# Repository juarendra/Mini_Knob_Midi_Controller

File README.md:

# Mini_Knob_Midi_Controller

## Preview Design 
<p align="center">

</p>
## Preview Product 
<p align="center">

</p>

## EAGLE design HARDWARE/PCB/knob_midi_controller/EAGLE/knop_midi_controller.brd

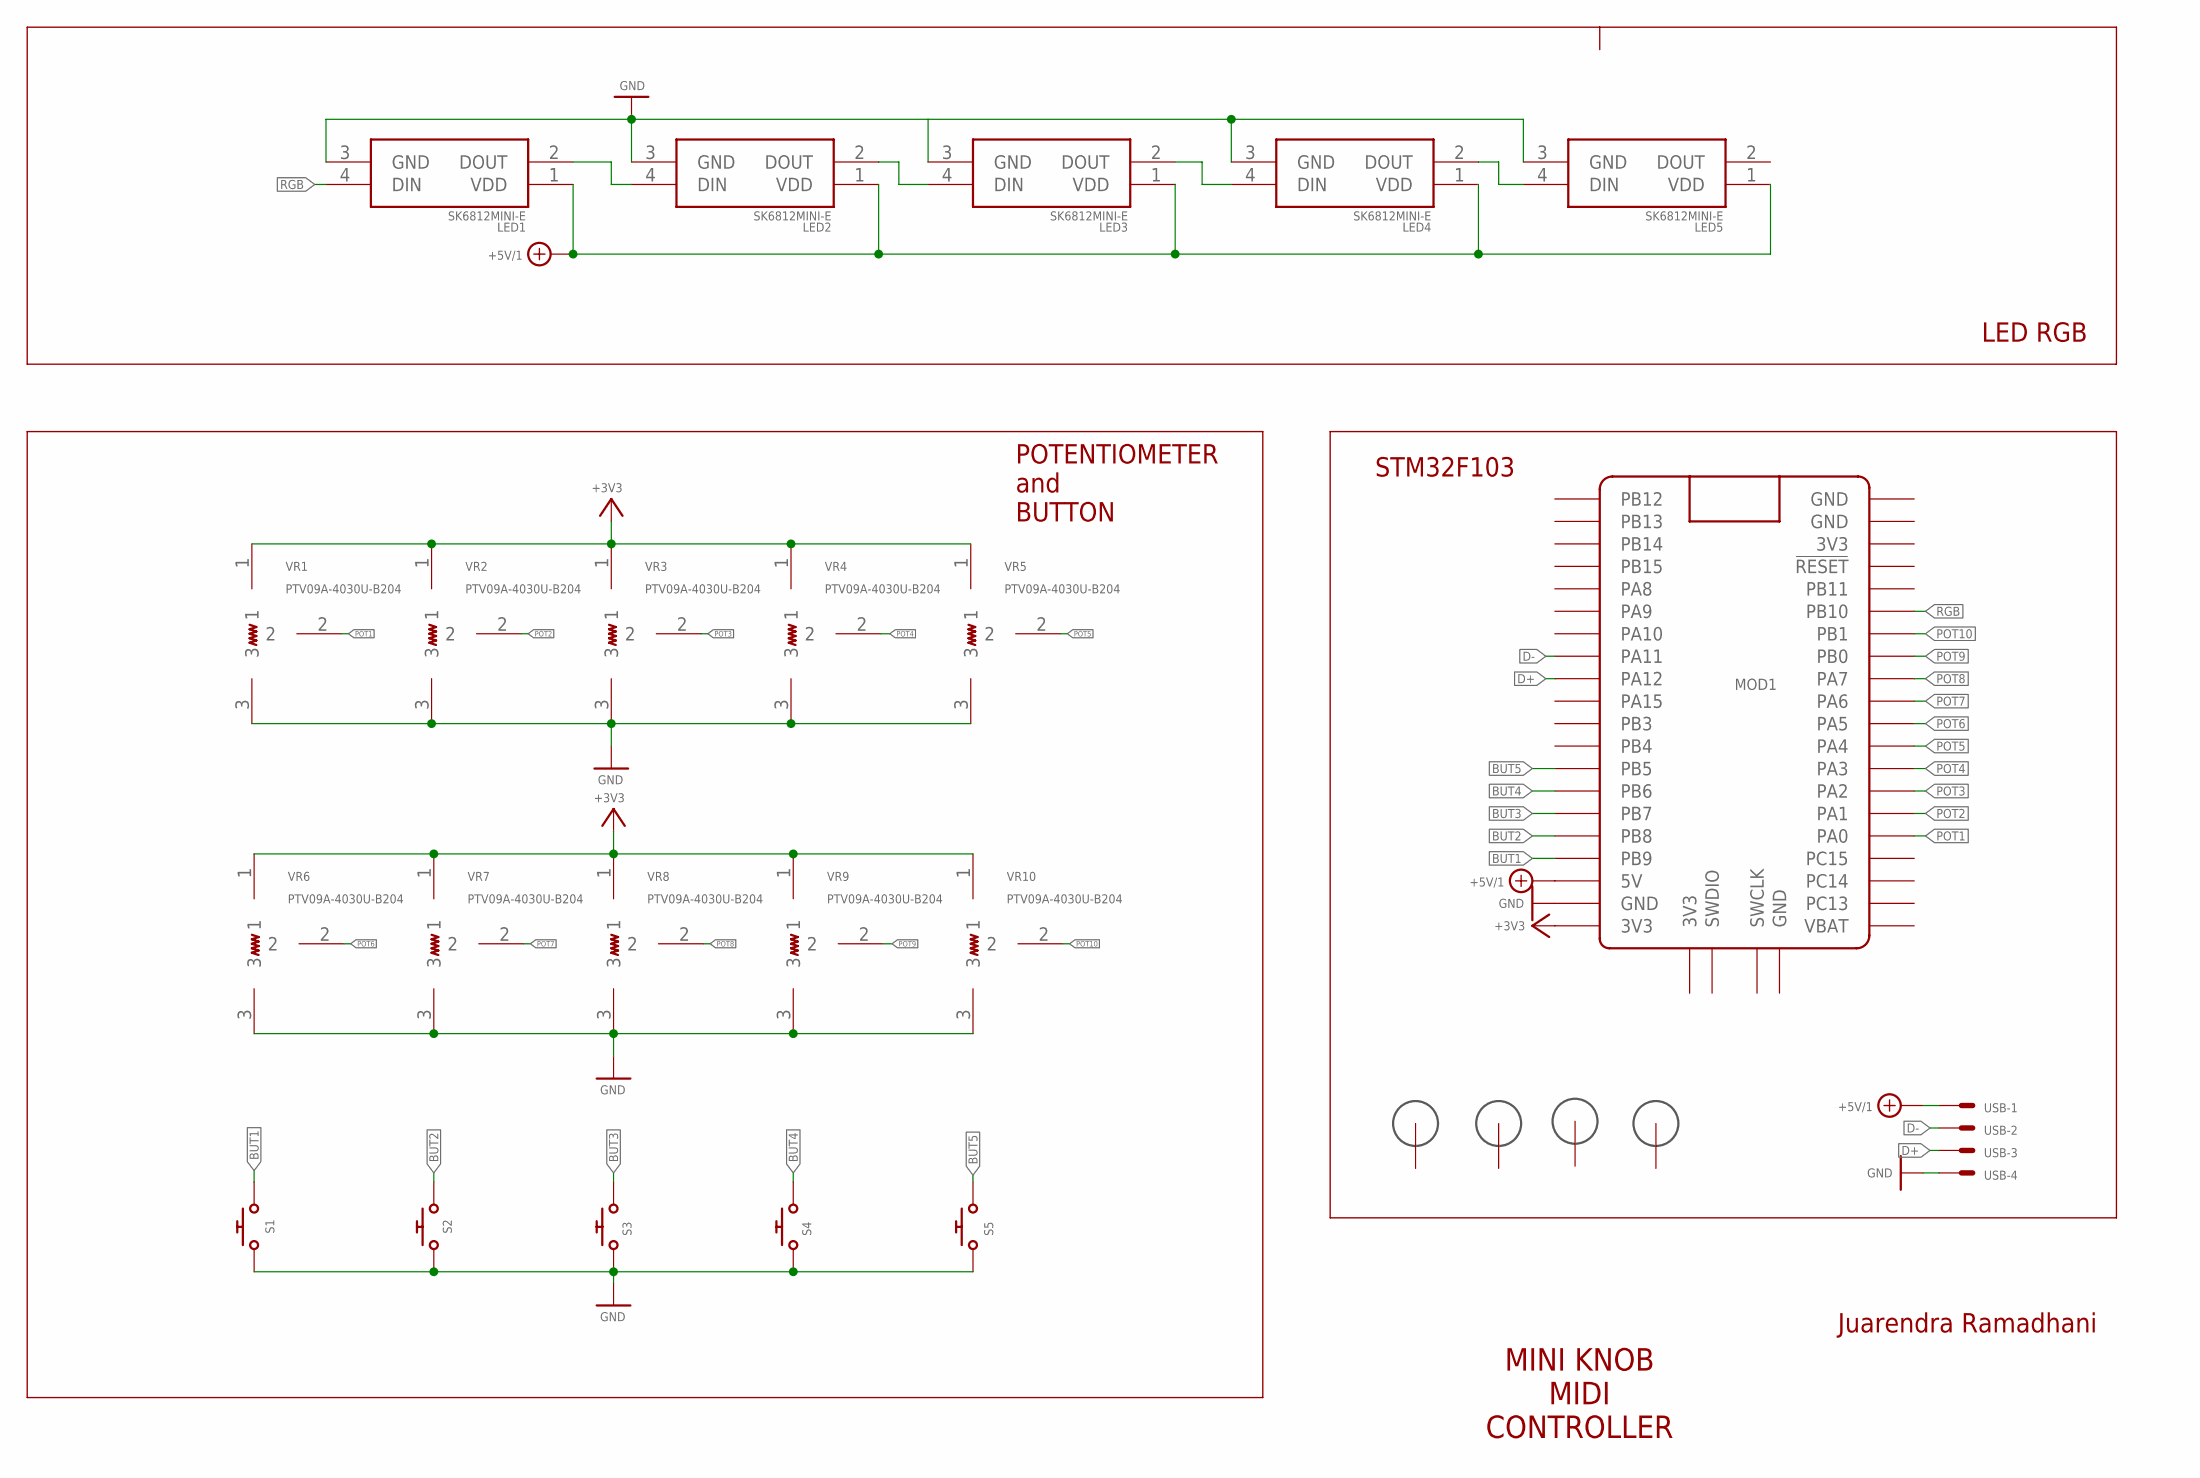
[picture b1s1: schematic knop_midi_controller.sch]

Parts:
H1, H2, H3, H4: 3MM_HOLE
LED1, LED2, LED3, LED4, LED5: SK6812MINI-E; SK6812MINIE
MOD1: BLUE_PILL
S1, S2, S3, S4, S5: CHERRY_MX_WITH_KEILWITH_KEIL; CHERRY_MX_WITH_KEIL
USB: 22-23-2041
VR1, VR2, VR3, VR4, VR5, VR6, VR7, VR8, VR9, VR10: PTV09A-4030U-B204; PTV09A4020FB103

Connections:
+3V3: MOD1.P$20 (3V3), VR1.1, VR2.1, VR3.1, VR4.1, VR5.1, VR6.1, VR7.1, VR8.1, VR9.1, VR10.1
+5V/1: LED1.1 (VDD), LED2.1 (VDD), LED3.1 (VDD), LED4.1 (VDD), LED5.1 (VDD), MOD1.P$18 (5V), USB.1
BUT1: MOD1.P$17 (PB9), S1.2
BUT2: MOD1.P$16 (PB8), S2.2
BUT3: MOD1.P$15 (PB7), S3.2
BUT4: MOD1.P$14 (PB6), S4.2
BUT5: MOD1.P$13 (PB5), S5.2
D+: MOD1.P$9 (PA12), USB.3
D-: MOD1.P$8 (PA11), USB.2
GND: LED1.3 (GND), LED2.3 (GND), LED3.3 (GND), LED4.3 (GND), LED5.3 (GND), MOD1.P$19 (GND), S1.1, S2.1, S3.1, S4.1, S5.1, USB.4, VR1.3, VR2.3, VR3.3, VR4.3, VR5.3, VR6.3, VR7.3, VR8.3, VR9.3, VR10.3
unnamed: LED1.2 (DOUT), LED2.4 (DIN)
unnamed: LED2.2 (DOUT), LED3.4 (DIN)
unnamed: LED3.2 (DOUT), LED4.4 (DIN)
unnamed: LED4.2 (DOUT), LED5.4 (DIN)
POT1: MOD1.P$36 (PA0), VR1.2
POT2: MOD1.P$35 (PA1), VR2.2
POT3: MOD1.P$34 (PA2), VR3.2
POT4: MOD1.P$33 (PA3), VR4.2
POT5: MOD1.P$32 (PA4), VR5.2
POT6: MOD1.P$31 (PA5), VR6.2
POT7: MOD1.P$30 (PA6), VR7.2
POT8: MOD1.P$29 (PA7), VR8.2
POT9: MOD1.P$28 (PB0), VR9.2
POT10: MOD1.P$27 (PB1), VR10.2
RGB: LED1.4 (DIN), MOD1.P$26 (PB10)

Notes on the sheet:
LED RGB
POTENTIOMETER and BUTTON
STM32F103
MINI KNOB MIDI CONTROLLER
Juarendra Ramadhani

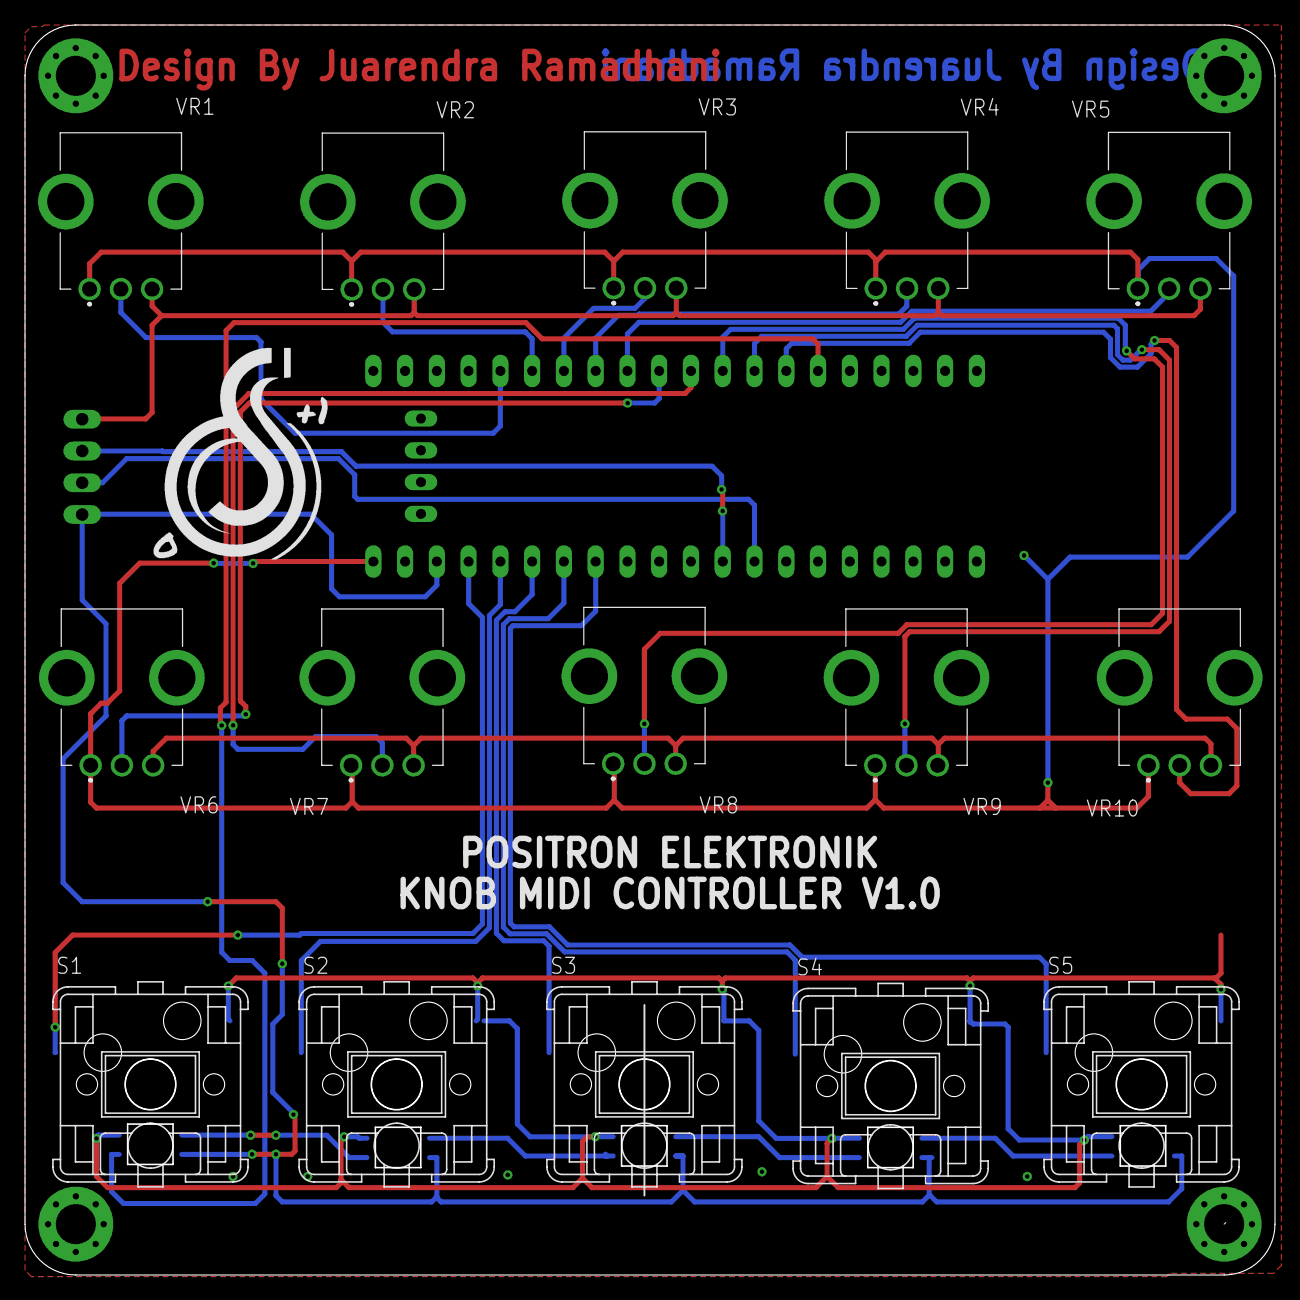
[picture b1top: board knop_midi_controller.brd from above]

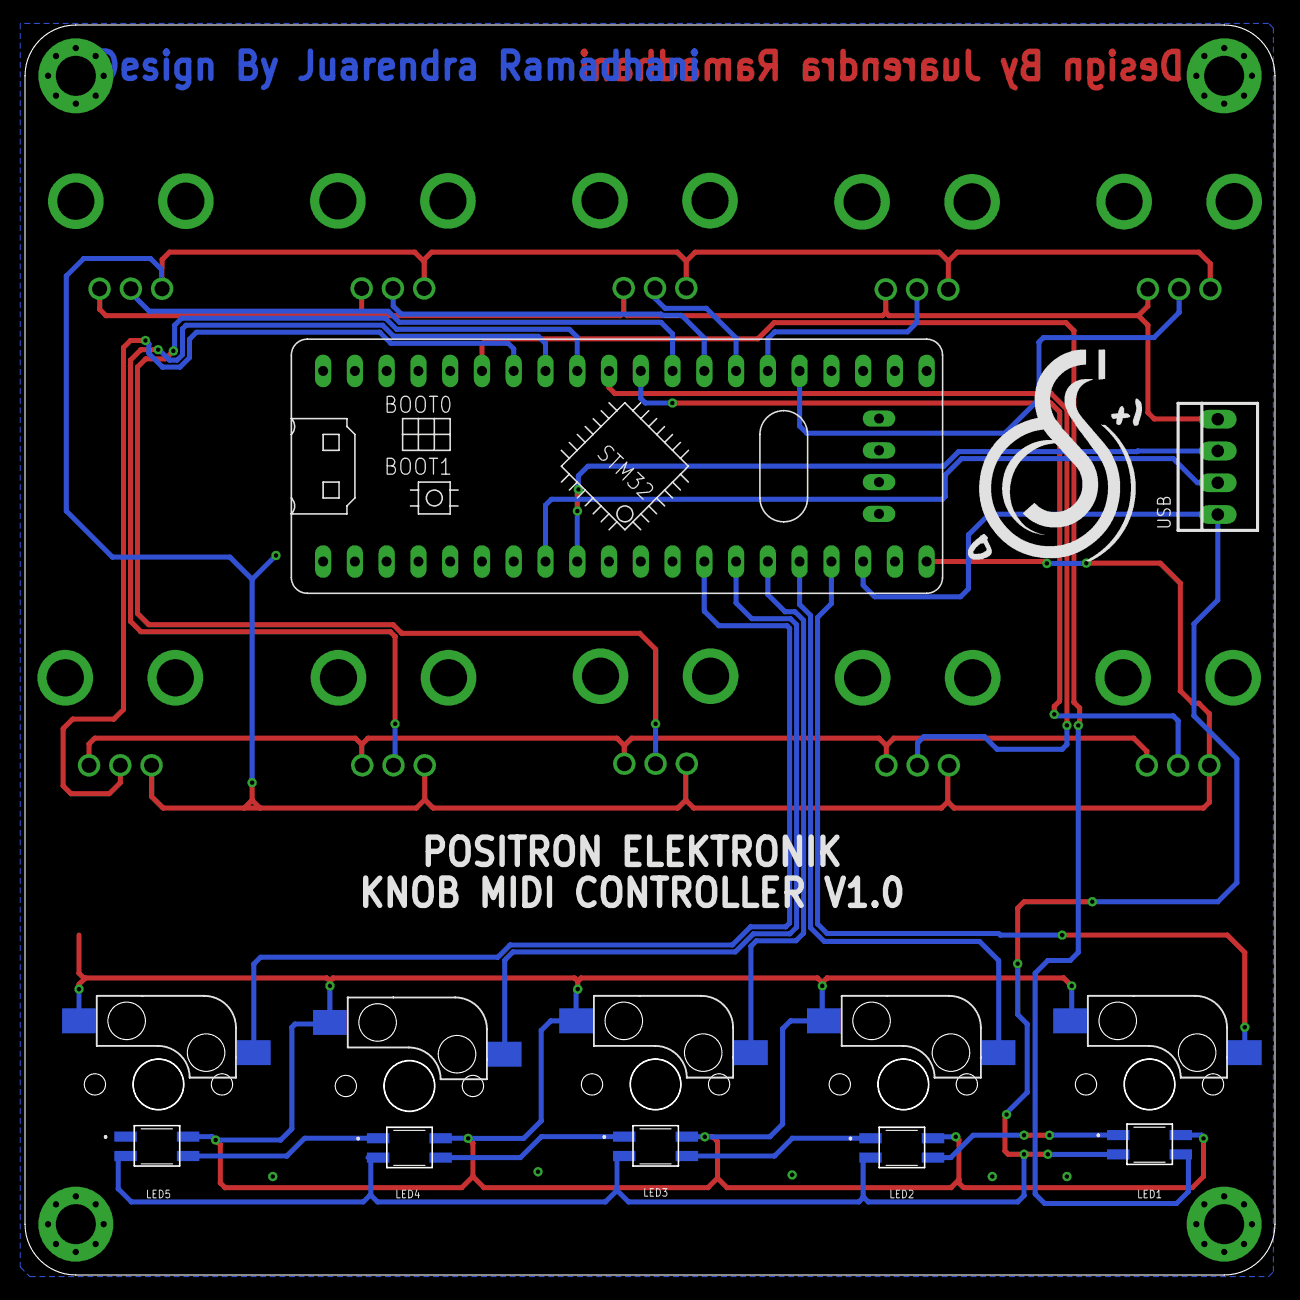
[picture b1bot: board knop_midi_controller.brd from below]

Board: 2 copper layers, 99.8 x 99.8 mm, 26 parts (8 on the bottom side), 25 nets.

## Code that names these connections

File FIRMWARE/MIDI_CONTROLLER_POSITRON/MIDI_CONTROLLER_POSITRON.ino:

#include <USBComposite.h>
USBMIDI midi;
//#include <ResponsiveAnalogRead.h> 
#include <FastLED.h>

#define LED_PIN     PB10        // Choose a tested pin
#define NUM_LEDS    5
#define BRIGHTNESS  100
#define LED_TYPE    WS2812B
#define COLOR_ORDER GRB

CRGB leds[NUM_LEDS];

const int NUM_POT = 10;
const int NUM_BUT = 5;
const int analogInputs[NUM_POT] = {PA0, PA1, PA2, PA3, PA4, PA5, PA6, PA7, PB0, PB1};
const int digitalInput[NUM_BUT] = {PB9, PB8, PB7, PB6, PB5};
int analogSliderValues[NUM_POT];
//ResponsiveAnalogRead responsivePot[NUM_POT] = {}; 
int potCState[NUM_POT] = { 0 };  // Current state of the pot
int potPState[NUM_POT] = { 0 };  // Previous state of the pot
int potVar = 0;                 // Difference between the current and previous state of the pot

int midiCState[NUM_POT] = { 0 };  // Current state of the midi value
int midiPState[NUM_POT] = { 0 };  // Previous state of the midi value
int reading_pot = 0;

const int TIMEOUT = 300;              // Amount of time the potentiometer will be read after it exceeds the varThreshold
const int varThreshold = 20;          // Threshold for the potentiometer signal variation
boolean potMoving = true;             // If the potentiometer is moving
unsigned long PTime[NUM_POT] = { 0 };  // Previously stored time
unsigned long timer[NUM_POT] = { 0 };  // Stores the time that has elapsed since the timer was reset

int potMin = 0;
int potMax = 3070;

bool debug_pot = false;
byte midiCh = 0;
byte cc = 1;   
byte NUM_BANK = 0;

const int NUM_SAMPLES = 10;

void setup() {
  FastLED.addLeds<LED_TYPE, LED_PIN, COLOR_ORDER>(leds, NUM_LEDS);
  FastLED.setBrightness(BRIGHTNESS);

  for (int i = 0; i < NUM_POT; i++) {
    pinMode(analogInputs[i], INPUT);
  }
  for (int i = 0; i < NUM_BUT; i++) {
    pinMode(digitalInput[i], INPUT_PULLUP);
  }
  if (debug_pot){
    Serial.begin(9600);
  }
  else{
    USBComposite.setProductId(0x0031);
    midi.begin();
    while (!USBComposite);
  }
}

void loop() {
  // Light up LEDs based on active bank
  for(int i = 0; i < NUM_LEDS; i++) {
    if (i == NUM_BANK) {
      leds[i] = CRGB::White;   // Active bank LED to white
    } else {
      leds[i] = CRGB::Black;   // Others off
    }
  }
  FastLED.show();

  for (int i = 0; i < NUM_BUT; i++){
    if (!digitalRead(digitalInput[i])){
      NUM_BANK = i;
    }

  }
  if(debug_pot){
    updateSliderValues();
    printSliderValues();
    delay(100);
  }
  else {
    sendMidiValue();
    delay(10);
  }
}

void sendMidiValue() {
  int potMin = 10;    
  int potMax = 3070;

  for (int i = 0; i < NUM_POT; i++) {
    int total = 0;

    // Take multiple samples to average
    for (int s = 0; s < NUM_SAMPLES; s++) {
      total += analogRead(analogInputs[i]);
      delayMicroseconds(100); // Small delay between reads
    }

    reading_pot = total / NUM_SAMPLES; // Calculate average reading
    potCState[i] = reading_pot;

    // Map and constrain stable average value
    midiCState[i] = map(potCState[i], potMin, potMax, 127, 0);
    midiCState[i] = constrain(midiCState[i], 0, 127);

    // Dead zones to further stabilize extremes
    if (midiCState[i] <= 1) midiCState[i] = 0;
    if (midiCState[i] >= 126) midiCState[i] = 127;

    potVar = abs(potCState[i] - potPState[i]);
    if (potVar > varThreshold) {
      PTime[i] = millis();
    }
    timer[i] = millis() - PTime[i];

    potMoving = timer[i] < TIMEOUT;

    // Only send MIDI if there is meaningful change
    if (abs(midiCState[i] - midiPState[i]) > 1) {
      midi.sendControlChange(midiCh, cc + i + (NUM_BANK * 10), midiCState[i]);
      potPState[i] = potCState[i];
      midiPState[i] = midiCState[i];
    }
  }
}

void updateSliderValues() {
  for (int i = 0; i < NUM_POT; i++) {
     analogSliderValues[i] = analogRead(analogInputs[i]);
  }
}

void printSliderValues() {
  for (int i = 0; i < NUM_POT; i++) {
    String printedString = String("Slider #") + String(i + 1) + String(": ") + String(analogSliderValues[i]) + String(" mV");
    Serial.write(printedString.c_str());

    if (i < NUM_POT - 1) {
      Serial.write(" | ");
    } else {
      Serial.write("\n");
    }
  }
}

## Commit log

2024-11-04 FEAT: add pcb
2024-11-05 FEAT: add 3d desain case, model and dimension
2024-11-05 FEAT: fix problem placement pcb and add name and logo
2024-11-06 FEAT: update gerber
2024-11-29 DOC: update readme for image midi controller
2025-05-19 FEAT: add firmware midi function
2025-05-28 FEAT: add init led rgb
2025-05-28 FEAT: add rgb as indicator bank
2025-05-29 FEAT: add sample reading pot
2025-05-29 FEAT: change brightness for seenable after add kkeycaps
2025-06-01 FEAT: add real image
2025-06-01 FEAT: Update README.md
2025-06-05 FEAT: add library led rgb controller
